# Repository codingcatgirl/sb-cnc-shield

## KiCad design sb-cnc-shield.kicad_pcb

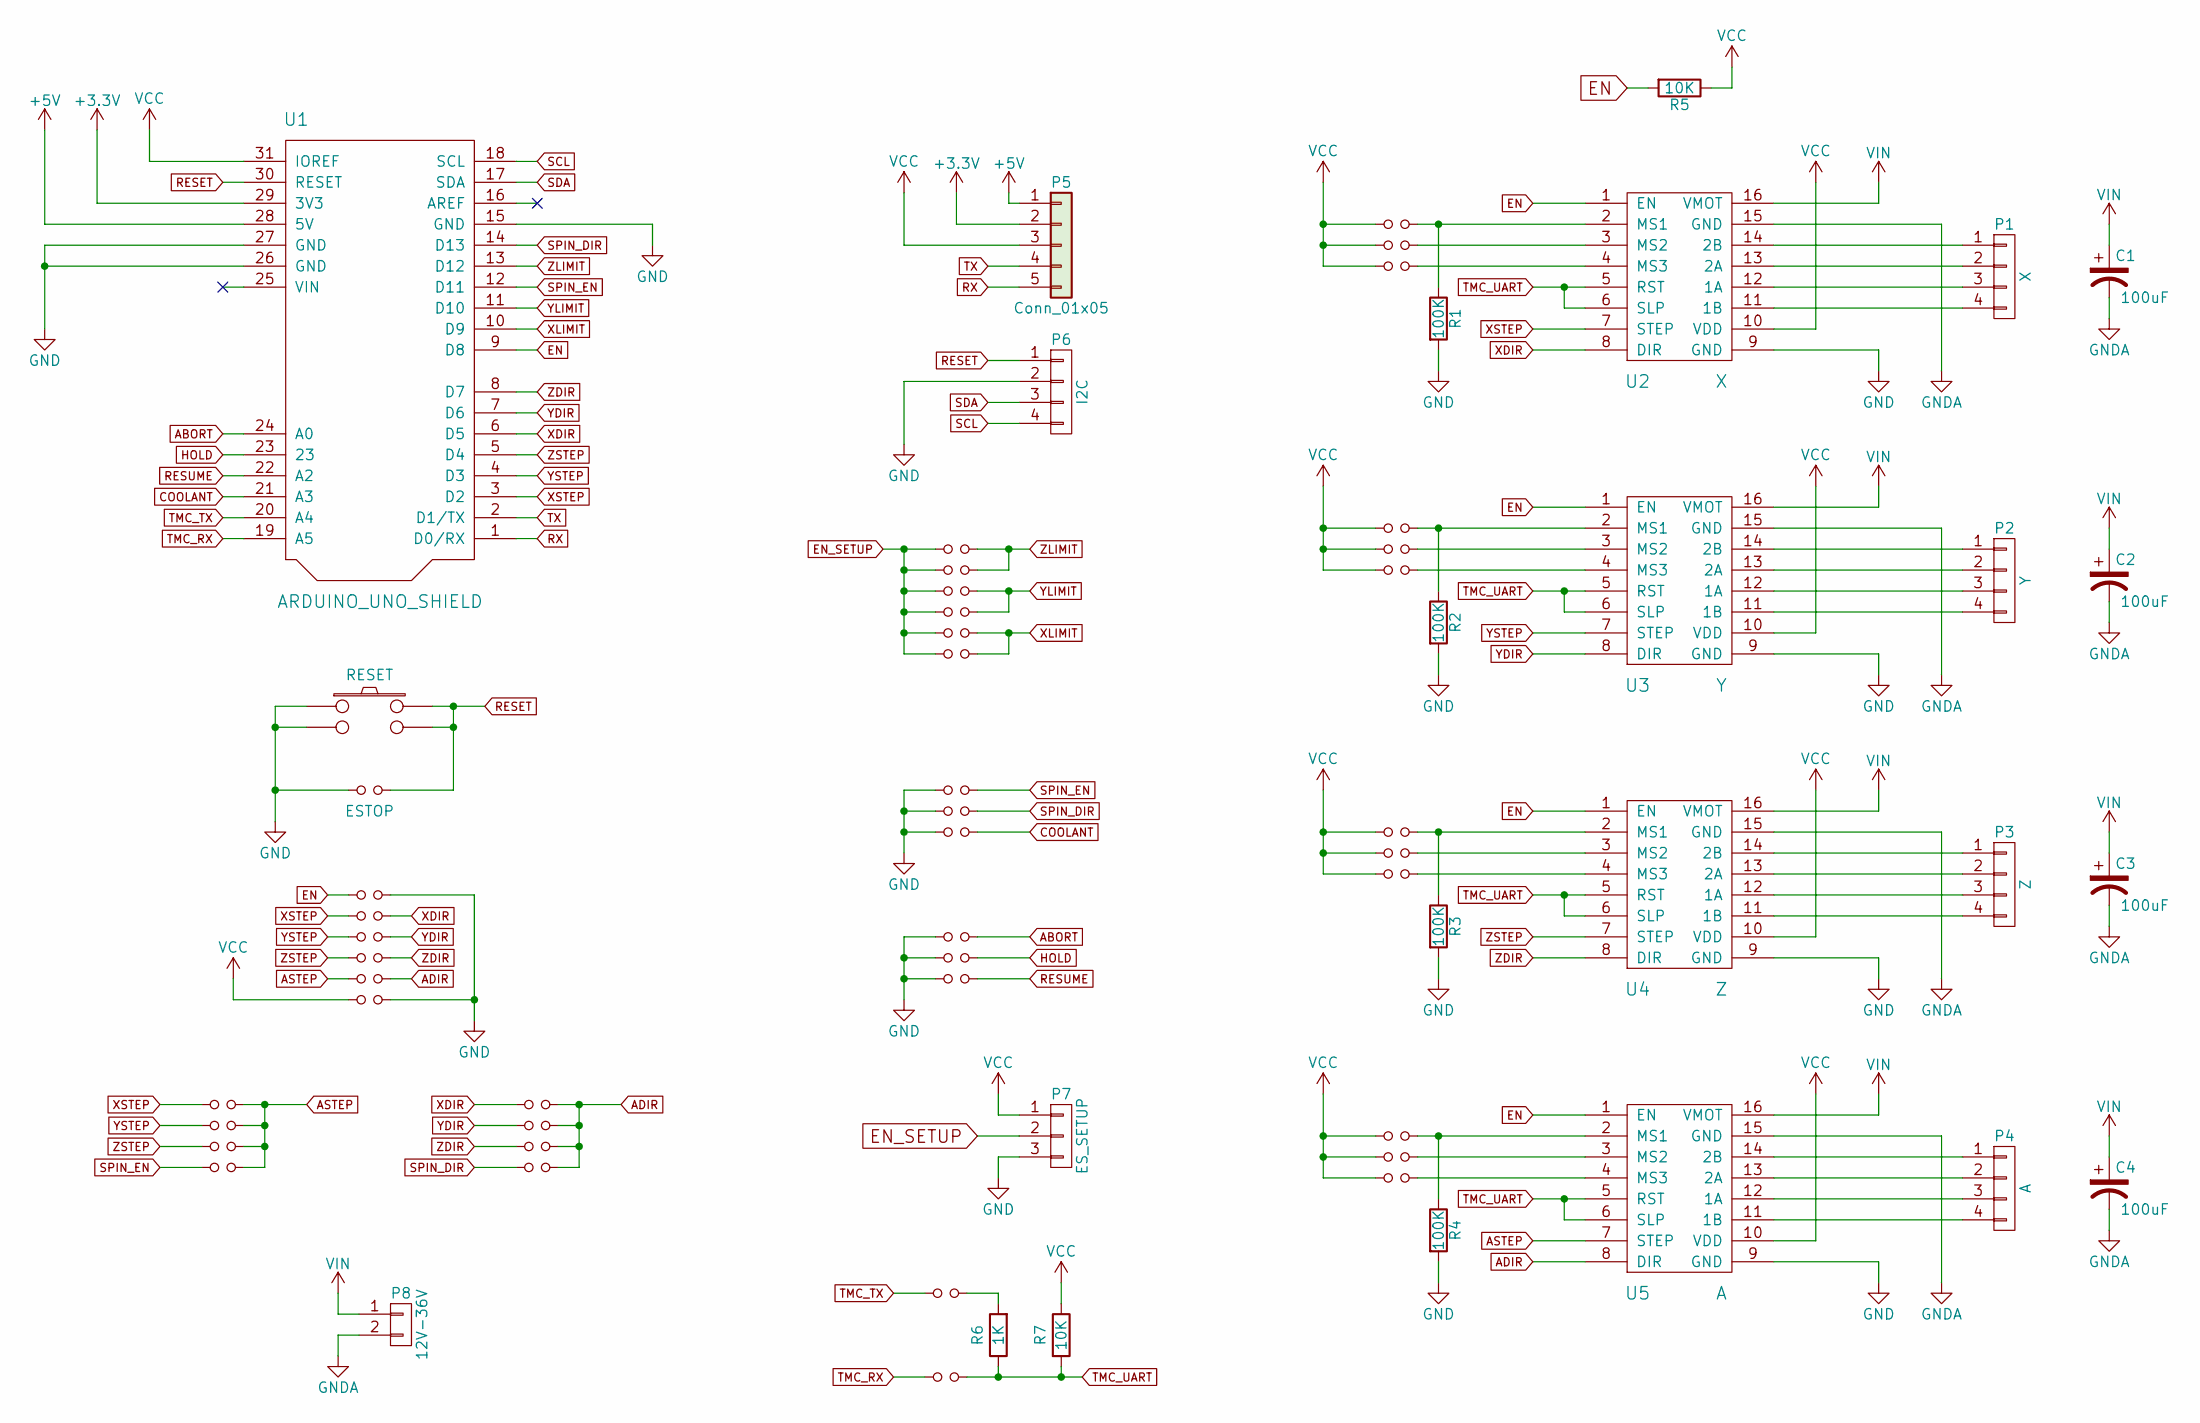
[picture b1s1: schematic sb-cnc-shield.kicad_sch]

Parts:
C1, C2, C3, C4: 100uF; c_elec_6.3x7.7
JP1, JP2, JP3, JP4, JP5, JP6, JP7, JP8, JP9, JP10, JP11, JP12, JP32, JP33, JP34, JP35, JP36, JP37, JP38, JP39: Jumper_NO_Small; Pin_100mil_Header_Straight_1x02
JP13: Z+; Pin_100mil_Header_Straight_1x02
JP14: Z-; Pin_100mil_Header_Straight_1x02
JP15: Y+; Pin_100mil_Header_Straight_1x02
JP16: Y-; Pin_100mil_Header_Straight_1x02
JP17: X+; Pin_100mil_Header_Straight_1x02
JP18: X-; Pin_100mil_Header_Straight_1x02
JP19: SEn; Pin_100mil_Header_Straight_1x02
JP20: SDir; Pin_100mil_Header_Straight_1x02
JP21: Cool; Pin_100mil_Header_Straight_1x02
JP22: Abort; Pin_100mil_Header_Straight_1x02
JP23: Hold; Pin_100mil_Header_Straight_1x02
JP24: Resume; Pin_100mil_Header_Straight_1x02
JP25: ESTOP; Pin_100mil_Header_Straight_1x02
JP26: EN/GND; Pin_100mil_Header_Straight_1x02
JP27: XSTEP/DIR; Pin_100mil_Header_Straight_1x02
JP28: YSTEP/DIR; Pin_100mil_Header_Straight_1x02
JP29: ZSTEP/DIR; Pin_100mil_Header_Straight_1x02
JP30: ASTEP/DIR; Pin_100mil_Header_Straight_1x02
JP31: VCC/GND; Pin_100mil_Header_Straight_1x02
JP40, JP41: Jumper_NO_Small; SolderJumper-2_P1.3mm_Open_TrianglePad1.0x1.5mm
P1: X; Pin_Header_Straight_2x04
P2: Y; Pin_Header_Straight_2x04
P3: Z; Pin_Header_Straight_2x04
P4: A; Pin_Header_Straight_2x04
P5: Conn_01x05; PinHeader_1x05_P2.54mm_Vertical
P6: I2C; Pin_Header_Straight_1x04
P7: ES_SETUP; Pin_Header_Straight_1x03
P8: 12V-36V; CONN_01x02_PITCH_5.08mm
R1, R2, R3, R4: 100K; R_0805
R5: 10K; R_0805
R6: 1K; R_0805_2012Metric
R7: 10K; R_0805_2012Metric
SW1: RESET; SWITCH_TACTILE_6.5_PTH
U1: ARDUINO_UNO_SHIELD; ARDUINO_SHIELD
U2: X; POLOLU_STEPPER_DRIVER
U3: Y; POLOLU_STEPPER_DRIVER
U4: Z; POLOLU_STEPPER_DRIVER
U5: A; POLOLU_STEPPER_DRIVER

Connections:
+3V3: P5.2, U1.29 (3V3)
+5V: P5.1, U1.28 (5V)
ABORT: JP22.2, U1.24 (A0)
ADIR: JP30.2, JP36.2, JP37.2, JP38.2, JP39.2, U5.8 (DIR)
ASTEP: JP30.1, JP32.2, JP33.2, JP34.2, JP35.2, U5.7 (STEP)
COOLANT: JP21.2, U1.21 (A3)
EN: JP26.1, R5.2, U1.9 (D8), U2.1 (EN), U3.1 (EN), U4.1 (EN), U5.1 (EN)
EN_SETUP: JP13.1, JP14.1, JP15.1, JP16.1, JP17.1, JP18.1, P7.2
GND: JP19.1, JP20.1, JP21.1, JP22.1, JP23.1, JP24.1, JP25.1, JP26.2, JP31.2, P6.2, P7.3, R1.2, R2.2, R3.2, R4.2, SW1.1, SW1.2, U1.15 (GND), U1.26 (GND), U1.27 (GND), U2.9 (GND), U3.9 (GND), U4.9 (GND), U5.9 (GND)
GNDA: C1.2, C2.2, C3.2, C4.2, P8.2, U2.15 (GND), U3.15 (GND), U4.15 (GND), U5.15 (GND)
HOLD: JP23.2, U1.23
unnamed: JP1.2, R1.1, U2.2 (MS1)
unnamed: JP2.2, U2.3 (MS2)
unnamed: JP3.2, U2.4 (MS3)
unnamed: JP4.2, R2.1, U3.2 (MS1)
unnamed: JP5.2, U3.3 (MS2)
unnamed: JP6.2, U3.4 (MS3)
unnamed: JP7.2, R3.1, U4.2 (MS1)
unnamed: JP8.2, U4.3 (MS2)
unnamed: JP9.2, U4.4 (MS3)
unnamed: JP10.2, R4.1, U5.2 (MS1)
unnamed: JP11.2, U5.3 (MS2)
unnamed: JP12.2, U5.4 (MS3)
unnamed: JP40.2, R6.2
unnamed: P1.1, U2.14 (2B)
unnamed: P1.2, U2.13 (2A)
unnamed: P1.3, U2.12 (1A)
unnamed: P1.4, U2.11 (1B)
unnamed: P2.1, U3.14 (2B)
unnamed: P2.2, U3.13 (2A)
unnamed: P2.3, U3.12 (1A)
unnamed: P2.4, U3.11 (1B)
unnamed: P3.1, U4.14 (2B)
unnamed: P3.2, U4.13 (2A)
unnamed: P3.3, U4.12 (1A)
unnamed: P3.4, U4.11 (1B)
unnamed: P4.1, U5.14 (2B)
unnamed: P4.2, U5.13 (2A)
unnamed: P4.3, U5.12 (1A)
unnamed: P4.4, U5.11 (1B)
RESET: JP25.2, P6.1, SW1.3, SW1.4, U1.30 (RESET)
RESUME: JP24.2, U1.22 (A2)
RX: P5.5, U1.1 (D0/RX)
SCL: P6.4, U1.18 (SCL)
SDA: P6.3, U1.17 (SDA)
SPIN_DIR: JP20.2, JP39.1, U1.14 (D13)
SPIN_EN: JP19.2, JP35.1, U1.12 (D11)
TMC_RX: JP41.1, U1.19 (A5)
TMC_TX: JP40.1, U1.20 (A4)
TMC_UART: JP41.2, R6.1, R7.2, U2.5 (RST), U2.6 (SLP), U3.5 (RST), U3.6 (SLP), U4.5 (RST), U4.6 (SLP), U5.5 (RST), U5.6 (SLP)
TX: P5.4, U1.2 (D1/TX)
VCC: JP1.1, JP2.1, JP3.1, JP4.1, JP5.1, JP6.1, JP7.1, JP8.1, JP9.1, JP10.1, JP11.1, JP12.1, JP31.1, P5.3, P7.1, R5.1, R7.1, U1.31 (IOREF), U2.10 (VDD), U3.10 (VDD), U4.10 (VDD), U5.10 (VDD)
VIN: C1.1, C2.1, C3.1, C4.1, P8.1, U2.16 (VMOT), U3.16 (VMOT), U4.16 (VMOT), U5.16 (VMOT)
XDIR: JP27.2, JP36.1, U1.6 (D5), U2.8 (DIR)
XLIMIT: JP17.2, JP18.2, U1.10 (D9)
XSTEP: JP27.1, JP32.1, U1.3 (D2), U2.7 (STEP)
YDIR: JP28.2, JP37.1, U1.7 (D6), U3.8 (DIR)
YLIMIT: JP15.2, JP16.2, U1.11 (D10)
YSTEP: JP28.1, JP33.1, U1.4 (D3), U3.7 (STEP)
ZDIR: JP29.2, JP38.1, U1.8 (D7), U4.8 (DIR)
ZLIMIT: JP13.2, JP14.2, U1.13 (D12)
ZSTEP: JP29.1, JP34.1, U1.5 (D4), U4.7 (STEP)

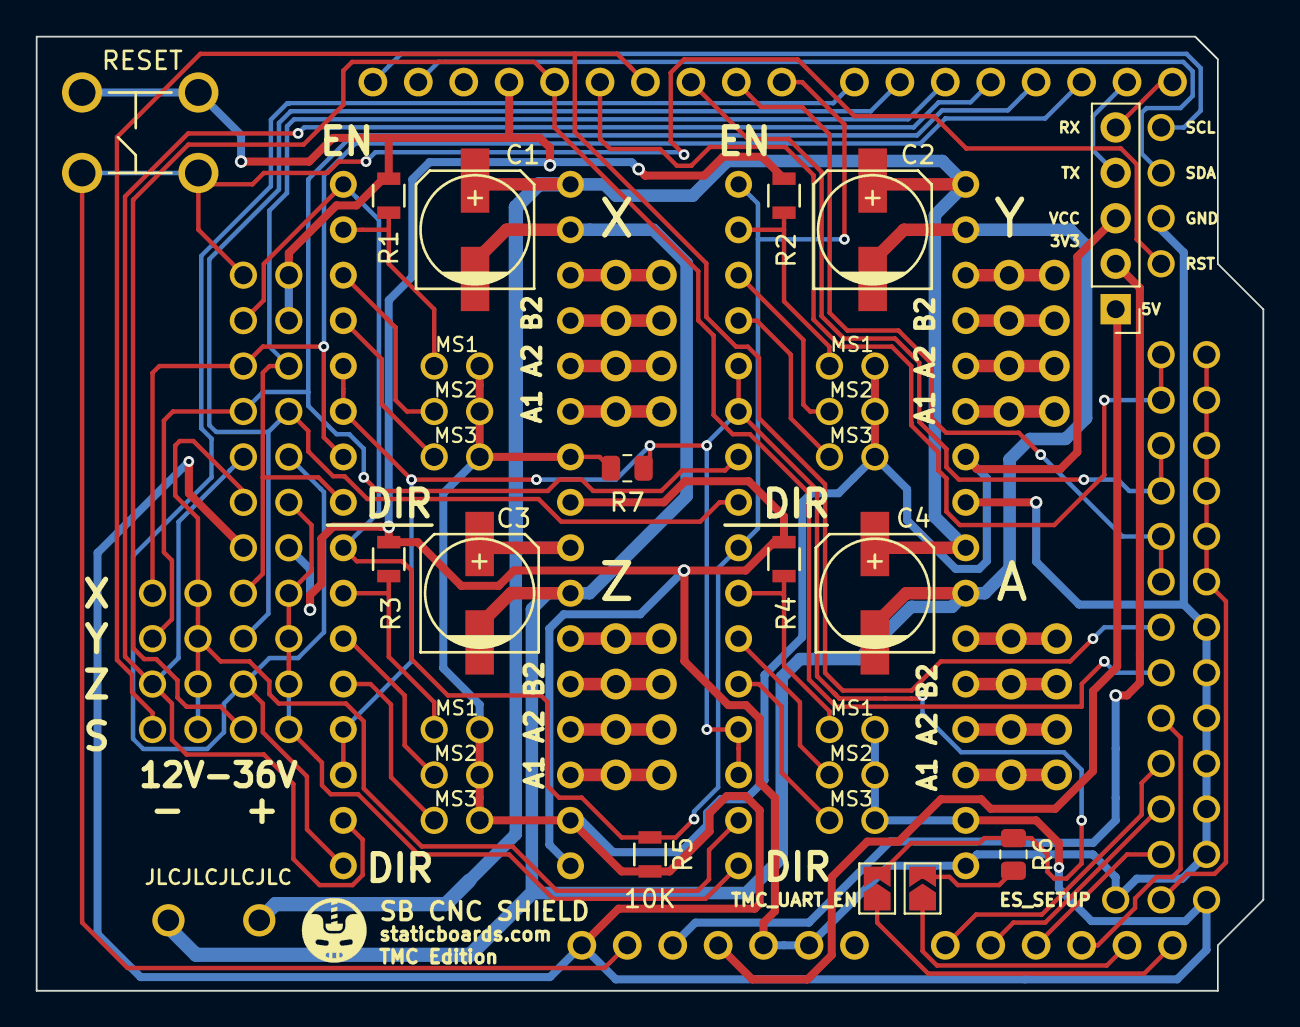
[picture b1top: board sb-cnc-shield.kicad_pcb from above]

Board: 2 copper layers, 68.6 x 53.3 mm, 66 parts (0 on the bottom side), 62 nets.

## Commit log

2022-01-07 add missing pins to arduino shield symbol
2022-01-07 add missing prints to shield footprint
2022-01-07 actually properly update shield footprint
2022-01-07 reroute correctly to VCC
2022-01-07 make some space for more pins
2022-01-07 use the real scl/sda pins
2022-01-07 more changes
2022-01-07 run DRC
2022-01-07 adjust to jlcpcb design rules
2022-01-07 some more small edits
2022-01-08 3d models
2022-08-17 update 3d models
